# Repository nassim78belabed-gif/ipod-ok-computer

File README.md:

# iPod OK Computer Edition : ESP32-S3

Un iPod Classic refait de zéro : lecteur MP3 sur carte SD, écran couleur 2,4", DAC I2S et 6 boutons, pour environ 33 € de composants. Firmware, PCB (2 cartes) et boîtier 3D sont conçus de bout en bout, de la lecture des tags ID3 au transfert de musique par WiFi.

> Projet repris de zéro en septembre 2026 avec un nouveau brochage (firmware fonctionnel sur breadboard depuis fin septembre).

## Ce que j'ai fait

- **Firmware** en C++ (Arduino / ESP32) : navigation Artistes / Albums / Morceaux, lecture MP3 en I2S, pochettes, lecture des tags ID3.
- **Transfert de musique par WiFi** depuis un téléphone ou un PC, avec rangement automatique d'après les tags.
- **PCB** en deux cartes, générées par script, avec leurs fichiers de fabrication.
- **Boîtier** en deux coques, généré en CadQuery à partir des cotes des PCB.
- **Easter eggs** par album (thèmes, messages, code secret aux boutons).

## Matériel

| Composant | Détail |
|---|---|
| Microcontrôleur | ESP32-S3-DevKitC-1 **N16R8** (16 Mo flash, 8 Mo PSRAM octal) |
| Écran | ILI9341 2,4" 240x320 SPI, module avec lecteur SD intégré (tactile non utilisé) |
| Audio | DAC I2S PCM5102A (module **CJMCU-5102**, 11 broches), sortie jack LINE OUT |
| Commandes | 6 boutons poussoirs vers GND (pull-up interne) |

## Coût

Prix indicatifs (AliExpress / Amazon).

| Composant | Prix |
|---|---|
| ESP32-S3-DevKitC-1 N16R8 | ~8 € |
| Écran ILI9341 2,4" avec lecteur SD | ~8 € |
| DAC PCM5102A (module CJMCU-5102) | ~5 € |
| Carte microSD 32 Go | ~5 € |
| 6 boutons poussoirs | ~2 € |
| Breadboard + fils (prototype) | ~5 € |
| **Total version breadboard** | **~33 €** |

Version finale V1, portable sur batterie :

| Composant | Prix |
|---|---|
| ESP32, écran, DAC, microSD, boutons (voir ci-dessus) | ~28 € |
| Batterie LiPo YL 603450 (3,7 V, 1200 mAh, protégée) | ~8 € |
| Chargeur TP4056 | ~1 € |
| Régulateur 3,3 V, interrupteur, prise JST | ~3 € |
| PCB (2 cartes, fabrication type JLCPCB) | ~10 € |
| Boîtier imprimé en 3D | ~15 € |
| **Total version portable V1** | **~65 €** |

La V2 (molette cliquable iPod 4G à la place des boutons) ajoute le prix de la molette : ~10 à 15 € d'occasion.

## Fonctionnalités

Validées sur breadboard (firmware `firmware/ipod/`) :
- **Menus** Artistes / Albums / Morceaux, écran **Lecture en cours** (pochette, progression, volume), enchaînement des morceaux, pause, précédent / suivant, avance rapide.
- **Pochettes** : image intégrée au MP3, `/covers/<album>.jpg|.bmp`, `cover.jpg` / `folder.jpg` du dossier ; les JPG sont redimensionnés pour remplir le cadre.
- **Transfert MP3 par WiFi** : menu « Transfert MP3 », envoi de plusieurs MP3 d'un coup depuis un téléphone ou un PC, rangement automatique dans `/Music/<artiste>/<album>/` d'après les tags. Le WiFi n'est allumé que dans ce menu.
- **Easter eggs par album** : thème de couleurs, messages sur certaines pistes (fixes, défilants, « glitch ») et code secret aux boutons, décrits dans un fichier `easter.txt` par album (voir le dossier `easter/`).
- **Commandes série** : mêmes actions que les boutons (`m p < > + -`) et maintenance de la SD (liste, suppression, diagnostic des tags), via `outils/serie.py`.

Volume limité à 19/21 (au-delà, la sortie du DAC sature) ; départ à 16.

## Difficultés rencontrées

- **Écran et SD sur le même bus SPI.** L'ILI9341 ne libère pas sa broche SDO et bloquait la SD. Solution : le MISO de l'écran n'est pas câblé, et le firmware relâche toujours un CS avant d'activer l'autre.
- **Broches interdites.** Avec la PSRAM octal du N16R8, les GPIO 26 à 37 sont réservés : le brochage a dû être refait autour de cette contrainte.
- **Crash de la bibliothèque audio.** Certains MP3 provoquaient une division par zéro dans ESP32-audioI2S. J'ai corrigé la bibliothèque et gardé une copie patchée dans le dépôt (voir `LISEZMOI.md` du dossier).
- **WiFi et audio.** Le WiFi perturbait le son, donc il n'est allumé que dans le menu de transfert.
- **Saturation du DAC.** Au-delà de 19/21, la sortie sature : le volume est plafonné.
- **Passage au PCB.** Les cartes sont générées par script plutôt que dessinées à la main, ce qui permet de modifier le brochage et de régénérer tout le routage d'un coup.

## Brochage

| Fonction | GPIO |
|---|---|
| SPI SCK / MOSI / MISO (écran + SD) | 8 / 17 / 18 |
| SD CS | 16 |
| TFT CS / DC / RST | 11 / 9 / 10 |
| I2S BCK / DIN / LRCK | 7 / 6 / 5 |
| Boutons MENU / PLAY / PREV / NEXT / VOL+ / VOL- | 42 / 41 / 40 / 39 / 38 / 1 |

Rétroéclairage de l'écran sur 3V3 direct. Détails et contraintes : [hardware/wiring.md](hardware/wiring.md).

## PCB et boîtier

- **PCB v_final1** ([hardware/pcb_v_final1](hardware/pcb_v_final1/LISEZ-MOI.md)) : 2 cartes reliées par câble.
  - Carte logique (77 x 95 mm) : ESP32-S3 DevKit + PCM5102A + connecteurs vers l'écran, la SD et la façade boutons.
  - Carte façade (42,6 x 72,2 mm) : les 6 boutons en grille 2x3.
  - Le module écran ILI9341+SD reste externe, câblé à la carte logique.
  - Les cartes sont générées par script (`generateur/`) et les fichiers KiCad du PCB sont dans `kicad/`. [CONNEXIONS.md](hardware/pcb_v_final1/CONNEXIONS.md) liste toutes les connexions et tient lieu de schéma.
- **Boîtier v1** ([hardware/boitier_v1](hardware/boitier_v1/LISEZ-MOI.md)) : 2 coques (avant + arrière), 83 x 131 x 27 mm, générées en CadQuery à partir des cotes des PCB. **Provisoire** : plus large que le PCB pour laisser place à un écran et à des accessoires.

## Avancement

| Étape | État |
|---|---|
| Carte : puce, flash 16 Mo, PSRAM 8 Mo | ✅ testé (`test_carte`) |
| 1. SD : montage, liste, écriture/relecture | ✅ testé (`test_sd`, `liste_sd`) |
| Lecture des tags ID3 et du format MP3 | ✅ testé (`tags_sd`) |
| 2. Écran + SD + pochette | ✅ testé (`test_ecran_sd`) |
| 3. Boutons avec anti-rebond | ⏳ géré par le firmware, test dédié prêt (`test_boutons`) mais pas lancé |
| 4. Lecture MP3 vers le PCM5102A en I2S | ✅ testé (`test_bip`, `test_audio`) |
| 5. Interface iPod : Artistes, Albums, Morceaux, Lecture en cours, volume | ✅ firmware `firmware/ipod/` |
| 6. Transfert MP3 par WiFi | ✅ validé (25 MP3, ~0,3 Mo/s) |
| Easter eggs par album | ✅ essayés sur la carte |
| Améliorations d'interface (moteur d'affichage en PSRAM, polices, Cover Flow, playlists…) | ⏳ prévues |
| PCB : support DAC 11 broches, alimentation, découplage, pistes I2S courtes | ⏳ corrections à faire avant fabrication |
| V1 sur batterie (LiPo YL 603450, chargeur, mesure de tension) | ⏳ à ajouter au PCB |
| V2 : molette cliquable iPod 4G | ⏳ plus tard |

Tests faits sur breadboard uniquement : le PCB n'est pas encore fabriqué.

## Compilation

Outils : Arduino IDE 2 ou [arduino-cli](https://arduino.github.io/arduino-cli/), core **esp32 by Espressif 3.x**.

Bibliothèques : **Adafruit ILI9341** (+ Adafruit GFX, Adafruit BusIO), **TJpg_Decoder** (pochettes JPG). Audio : **ESP32-audioI2S** (schreibfaul1) 4.0.0, **copie patchée incluse dans le dépôt** (`firmware/ipod/src/ESP32-audioI2S/`, correctif d'une division par zéro sur certains MP3, voir son `LISEZMOI.md`) : rien à installer pour le firmware principal.

Réglages de la carte :

| Option | Valeur |
|---|---|
| Carte | ESP32S3 Dev Module |
| PSRAM | OPI PSRAM |
| Flash Size | 16 Mo |
| Partition | 16M Flash (3MB APP/9.9MB FATFS) |
| USB CDC On Boot | selon le port USB, voir ci-dessous |

**USB CDC On Boot** dépend du port USB branché :
- port **« COM »** (puce CH343) : désactivé, `Serial` sort sur l'UART0 ;
- port **« USB »** (USB natif) : activé, `Serial` sort sur l'USB natif.

Le firmware et les sketches de test écrivent sur `Serial` et `Serial0` : les messages restent lisibles quel que soit le port.

Exemple avec arduino-cli (port COM10) :

```
arduino-cli compile -u -p COM10 --fqbn esp32:esp32:esp32s3:PSRAM=opi,FlashSize=16M,CDCOnBoot=default,PartitionScheme=app3M_fat9M_16MB firmware/ipod
```

Remplacer `CDCOnBoot=default` par `CDCOnBoot=cdc` pour activer le CDC.

## Firmware

`firmware/ipod/` : `ipod.ino` (navigation, audio, boutons), `bibliotheque.ino` (tags ID3), `ecran.ino` (affichage), `easter.ino` (easter eggs), `web.ino` + `page_web.h` (WiFi, transfert), `ipod.h` (réglages).

## Sketches de test

| Sketch | Rôle |
|---|---|
| `firmware/tests/test_carte` | Infos puce, flash, test PSRAM, état des broches boutons |
| `firmware/tests/test_sd` | Montage SD, taille, liste de la racine, écriture/relecture de `test.txt` |
| `firmware/tests/liste_sd` | Liste récursive de toute la carte SD |
| `firmware/tests/tags_sd` | Tags ID3 (v1, v2.2 à 2.4) et format MPEG des MP3 de `/Music` |
| `firmware/tests/test_ecran_sd` | Écran (couleurs, texte, pochette) + liste de la SD |
| `firmware/tests/test_boutons` | Les 6 boutons avec anti-rebond (prêt, pas encore lancé) |
| `firmware/tests/test_bip` | Bip I2S vers le DAC |
| `firmware/tests/test_audio` | Lecture d'un MP3 de la SD vers le DAC |

## Carte SD

- Format **FAT32**
- Musique rangée dans `/Music/Artiste/Album/`, fichiers MP3 avec tags ID3 complets (titre, artiste, album, numéro de piste)
- MP3 testés : MPEG1 Layer III, 44,1 ou 48 kHz, stéréo

Pour ajouter de la musique sans retirer la carte : menu **Transfert MP3** sur l'iPod, puis page web (l'adresse s'affiche à l'écran) ou `curl -F "f=@fichier.mp3" http://<adresse>/api/envoi`.

Pour de bons fichiers : albums achetés sans DRM (Bandcamp, Qobuz, 7digital) ou CD rippés (Exact Audio Copy, fre:ac), qui arrivent avec tags et pochette.

## Structure du dépôt

```
ipod-ok-computer/
├── firmware/
│   ├── ipod/          # Firmware principal
│   └── tests/         # Sketches de test (un dossier par sketch)
├── easter/            # Modèles de fichiers easter.txt (un par album) + aperçus
├── outils/            # Scripts : commandes série, encodage de CD, journal série
├── hardware/
│   ├── wiring.md      # Brochage et contraintes
│   ├── pcb_v_final1/  # PCB actuel : carte logique + carte boutons (KiCad, gerbers, générateurs)
│   │   └── CONNEXIONS.md  # Liste des connexions (tient lieu de schéma)
│   ├── boitier_v1/    # Boîtier provisoire (STEP/STL, script CadQuery gen_case.py)
│   └── archives/      # Anciennes versions (v7, v8, breakout clickwheel), référence uniquement
└── LICENSE
```

## Licence

Le projet est sous licence **GPL-3.0**, voir [LICENSE](LICENSE).

Le dossier `firmware/ipod/src/ESP32-audioI2S/` est une copie patchée de la bibliothèque [ESP32-audioI2S](https://github.com/schreibfaul1/ESP32-audioI2S) (schreibfaul1), également sous **GPL-3.0** : sa licence d'origine est conservée dans ce dossier. Le projet entier est donc publié sous GPL-3.0.

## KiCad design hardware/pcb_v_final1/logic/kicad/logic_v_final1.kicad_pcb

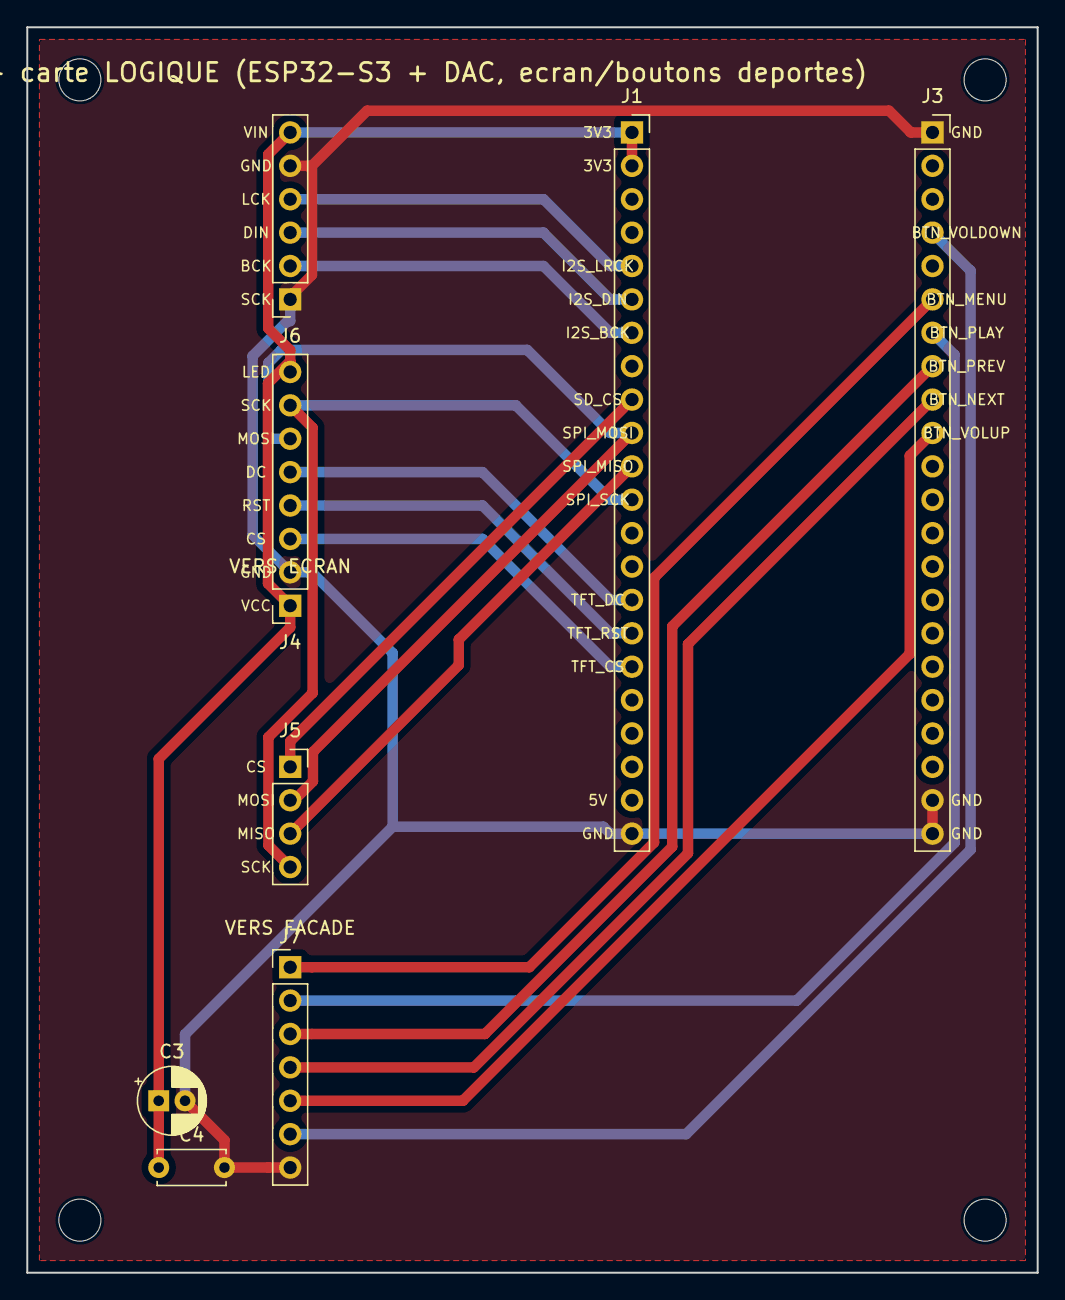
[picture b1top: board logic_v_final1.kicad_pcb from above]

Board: 2 copper layers, 76.9 x 94.7 mm, 12 parts (0 on the bottom side), 18 nets.

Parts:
C3: 10uF; CP_Radial_D5.0mm_P2.00mm
C4: 100nF; C_Disc_D5.0mm_W2.5mm_P5.00mm
H1, H2, H3, H4: MountingHole_3.2mm_M3
J1: ESP32-S3 J1 (gauche); PinSocket_1x22_P2.54mm_Vertical
J3: ESP32-S3 J3 (droite); PinSocket_1x22_P2.54mm_Vertical
J4: VERS ECRAN: VCC GND CS RST DC MOSI SCK LED; PinSocket_1x08_P2.54mm_Vertical
J5: VERS SD ecran; PinSocket_1x04_P2.54mm_Vertical
J6: PCM5102A: SCK BCK DIN LCK GND VIN; PinSocket_1x06_P2.54mm_Vertical
J7: VERS FACADE: MENU PLAY PREV NEXT VOL+ VOL- GND; PinHeader_1x07_P2.54mm_Vertical

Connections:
3V3: C3.1, C4.1, J1.1, J1.2, J4.1, J4.8, J6.6
BTN_MENU: J3.6, J7.1
BTN_NEXT: J3.9, J7.4
BTN_PLAY: J3.7, J7.2
BTN_PREV: J3.8, J7.3
BTN_VOLDOWN: J3.4, J7.6
BTN_VOLUP: J3.10, J7.5
GND: C3.2, C4.2, J1.22, J3.1, J3.21, J3.22, J4.2, J6.1, J6.5, J7.7
I2S_BCK: J1.7, J6.2
I2S_DIN: J1.6, J6.3
I2S_LRCK: J1.5, J6.4
SD_CS: J1.9, J5.1
SPI_MISO: J1.11, J5.3
SPI_MOSI: J1.10, J4.6, J5.2
SPI_SCK: J1.12, J4.7, J5.4
TFT_CS: J1.17, J4.3
TFT_DC: J1.15, J4.5
TFT_RST: J1.16, J4.4

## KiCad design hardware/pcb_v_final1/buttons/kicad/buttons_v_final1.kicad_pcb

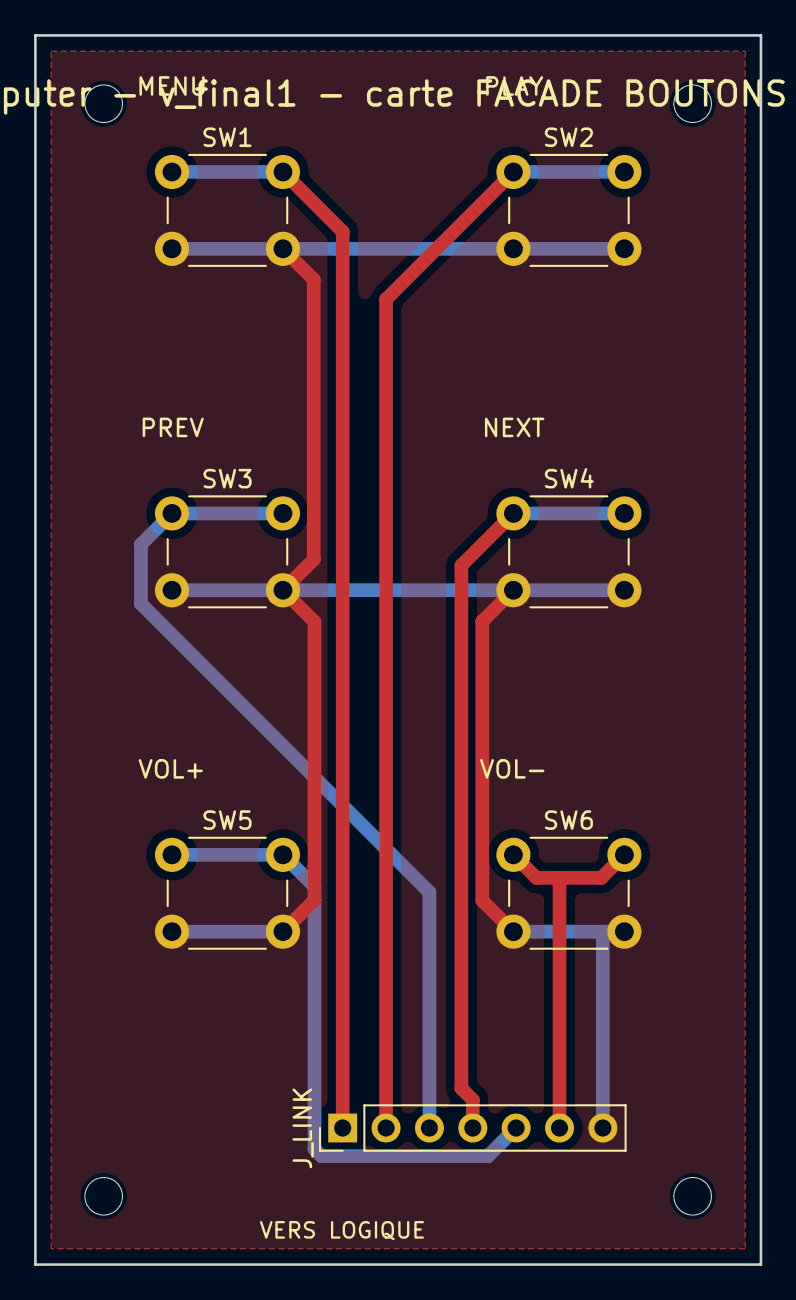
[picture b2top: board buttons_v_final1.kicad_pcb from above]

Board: 2 copper layers, 42.5 x 72.0 mm, 11 parts (0 on the bottom side), 7 nets.

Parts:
H1, H2, H3, H4: MountingHole_2.2mm_M2
J_LINK: VERS CARTE LOGIQUE; PinHeader_1x07_P2.54mm_Vertical
SW1: MENU; SW_PUSH_6mm
SW2: PLAY; SW_PUSH_6mm
SW3: PREV; SW_PUSH_6mm
SW4: NEXT; SW_PUSH_6mm
SW5: VOL+; SW_PUSH_6mm
SW6: VOL-; SW_PUSH_6mm

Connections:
BTN_MENU: J_LINK.1, SW1.1
BTN_NEXT: J_LINK.4, SW4.1
BTN_PLAY: J_LINK.2, SW2.1
BTN_PREV: J_LINK.3, SW3.1
BTN_VOLDOWN: J_LINK.6, SW6.1
BTN_VOLUP: J_LINK.5, SW5.1
GND: J_LINK.7, SW1.2, SW2.2, SW3.2, SW4.2, SW5.2, SW6.2

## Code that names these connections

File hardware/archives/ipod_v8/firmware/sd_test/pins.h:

// iPod "OK Computer Edition" - PCB V8 mini (sans batterie/molette) - ESP32-S3-DevKitC-1 N16R8
// Brochage EXACT du PCB (ne pas changer sans refaire le PCB).
// GPIO interdits sur N16R8 (PSRAM octale) : 26-37. Strapping evites : 0, 3, 45, 46.

// Bus SPI partage ecran + SD
#define SPI_SCK    8
#define SPI_MOSI   17
#define SPI_MISO   18      // = MISO de la SD uniquement (SDO de l'ecran NON connecte)

// Chip select / controle
#define SD_CS      16
#define TFT_CS     11
#define TFT_DC     9
#define TFT_RST    10

// DAC PCM5102A (I2S)
#define I2S_BCK    7
#define I2S_DIN    6
#define I2S_LRCK   5

// Boutons (internes en INPUT_PULLUP, boutons vers GND)
#define BTN_MENU     42
#define BTN_PLAY     41
#define BTN_PREV     40
#define BTN_NEXT     39
#define BTN_VOLUP    38
#define BTN_VOLDOWN  1

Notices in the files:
README.md:
License: GPL-3.0
